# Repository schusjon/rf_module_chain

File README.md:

# Overview

The aim of the project is to develop a chain of RF-modules which can be connected in series. The most common connector for RF applications is the SMA connector. Because of the high purchase price, the idea to use another connector e.g. PCI Express has existed for quite some time. The main advantage over other connectors is the comparatively low price. Moreover, it can be used up to a frequency of about 500 MHz and the male connector can be easily included on the circuit board. 

[Bild 1]: images/chain.PNG
![Alt-Text][Bild 1]

A means of digital communication should be implemented throughout the chain, an expansion that distinguishes this project from previous, unfinished attempts. The high amount of contacts the PCI-E connector provides facilitates this endeavor.
The chain starts with a special start-module including pin headers for the power supply, as will be explained later.
We expect that the following voltages will cover most conceivable scenarios:

Voltage Rails

|  +5V | -5V  |  3.3V | +12V  | -12V  |
|---|---|---|---|---|

Again, the chosen PCI connector allows for all those different voltage rails and with a current handling of 1A per pin, distributing power to the chain can be done with the same connector.
To feed the chain with the RF-Signal, one SMA connector on the start-module is unavoidable. For further experiments it is useful to add two additional RF inputs. 
These can be used for a reference signal or any auxiliary signal. In this project we limit ourselves to designing only the traces and basic interfacing for these signals on the boards. 
To receive the signal from the chain, a further SMA connecter is used on the end module. 

## Signal Chain

The signal chain consists of different modules, all of which have a few components and properties in common:
All links within the chain are established with PCI-E 36 connectors, all modules bear either a straddle mount receptacle, card-edge fingers or both to interface with neighboring modules.
Each one is equipped with a STM32F0 microprocessor for data transmission and control purposes. 
They utilize their internal RC oscillator to help minimize cost and prevent clock spill into the RF signals.
A 4pin header is used to program these processors with a ST-Link USB adaptor. A fifth pin adjacent to the programming connector serves in conjunction with a jumper as a power switch for the processor on this module only. 
Connected during normal operation, the jumper can be removed to shut off the processor of a single module without cutting the power of the rest of the chain. (Due to the nature of the daisy chain, communication will be interrupted as well)
The modules incorporate separate ground planes for RF and data/power circuits. 
The RF ground is continuous on the back of the PCB to improve impedance control. Via stitching and a defined trace width and aura (1mm width, 0.15mm aura) of the RF signal traces on the 1.6mm FR4 PCBs yield an impedance close to 50 Ohms (with the properties of the laminate causing deviations). 
A series of solder pads on the modules allow linking those ground planes at virtually any point in the chain if the need arises.

[Bild 2]: images/bottom.PNG
![Alt-Text][Bild 2]

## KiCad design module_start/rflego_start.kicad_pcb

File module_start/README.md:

# Start Module

**The input/start module** additionally features input connectivity for power and signals:

Standard 2.54mm pin headers serve as power inputs, thus allowing for easy assembly of custom breakout cables. The same holds true for the RX and TX signals, enabling the user to use his favorite UART converter or control the chain with a single board computer. Additional ground pins might be added in following revisions to facilitate interfacing.

The RF signal has a female SMA receptacle, the two additional signals (REF and AUX) terminate to solder pads that allow connection of coax cables or pin headers.

The input module also hosts a 3.3V regulator that supplies the whole chain. Solder pads are prepared for different types of SOT 23-5 LDOs with their respective circuitry.

At the moment, the installed processor does not add any exclusive functionality and is simply another link in the daisy chain. A possible future implementation would be the detection of input signals or power supply voltages to help troubleshoot larger experimental setups. Conversely, this component could be cut entirely for cost optimization. Especially with suitable detectors like the AD 8307 being in the 10€ price range.

[Bild 1]: images/start_description.PNG

![Alt-Text][Bild 1]

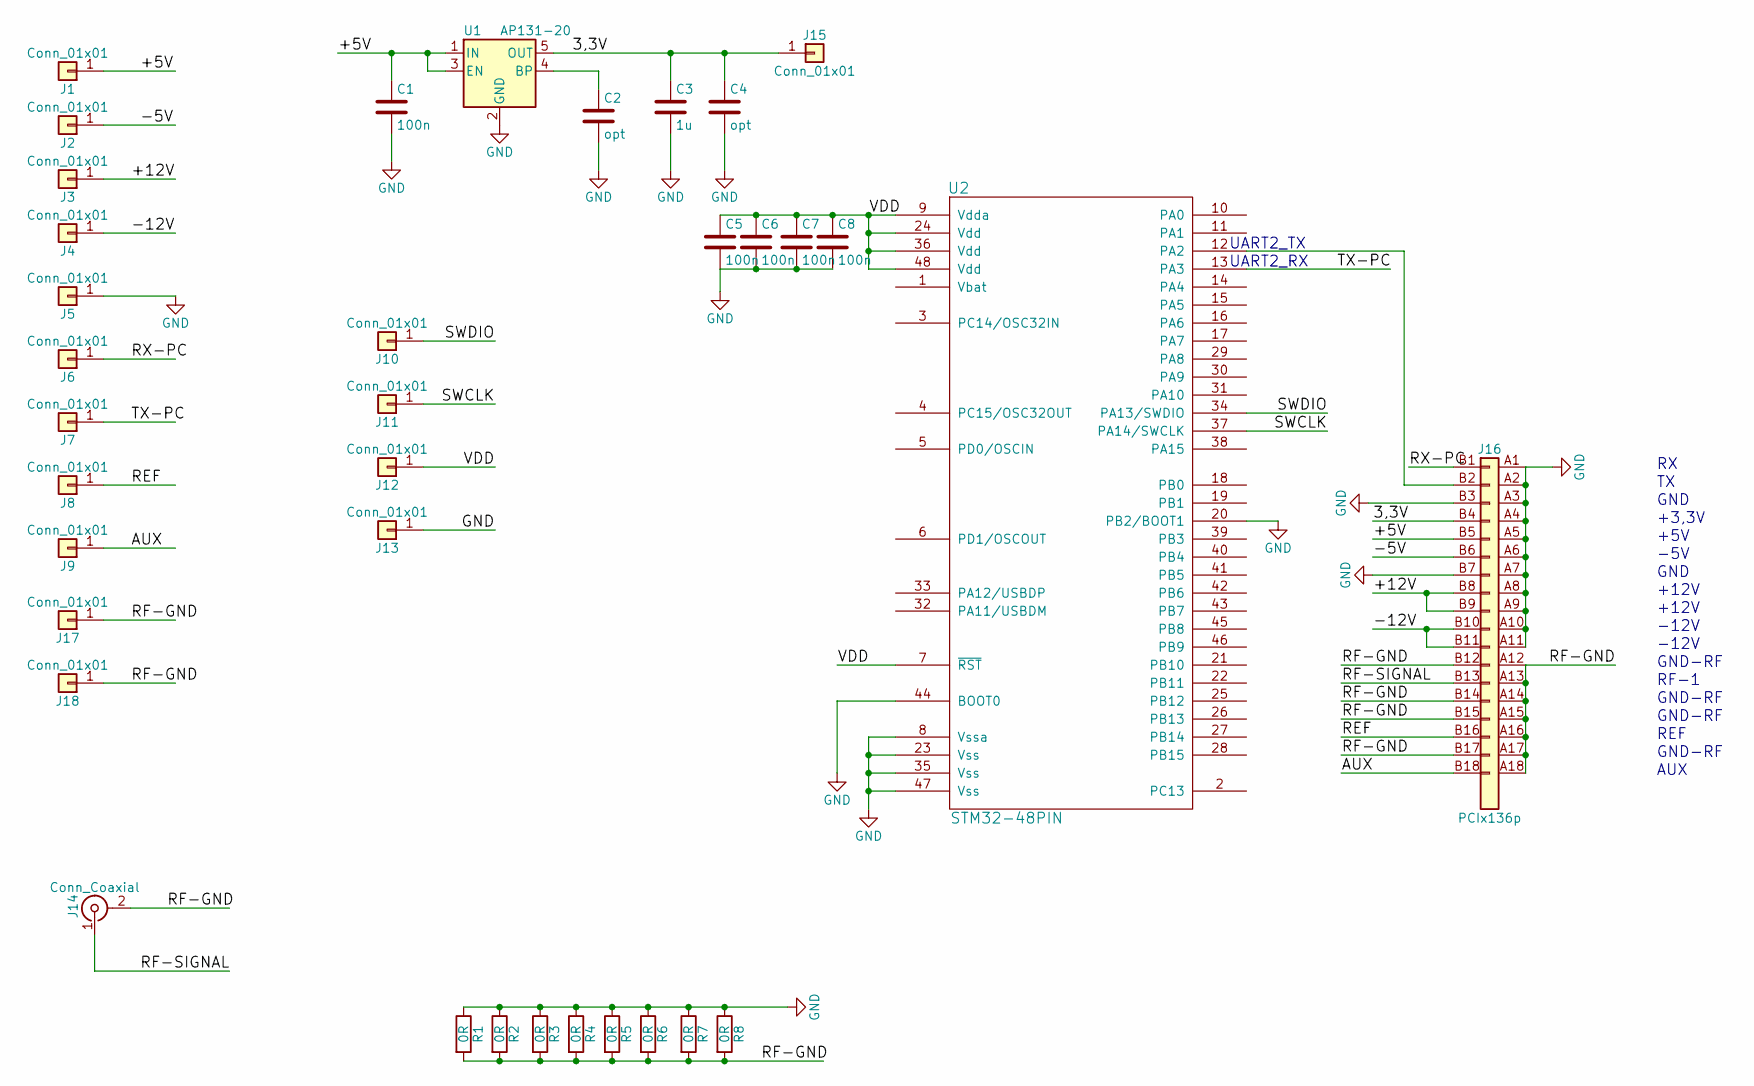
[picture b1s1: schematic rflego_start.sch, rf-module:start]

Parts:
C1, C5, C6, C7, C8: 100n; C_0603_HandSoldering
C2, C4: opt; C_0603_HandSoldering
C3: 1u; C_0603_HandSoldering
J1, J2, J3, J4, J5, J6, J7, J8, J9, J10, J11, J12, J13, J15, J17, J18: Conn_01x01; Pin_Header_Straight_1x01_Pitch2.54mm
J14: Conn_Coaxial; CONSMAEDGE
J16: PCIx136p; PCI-EXPRESS-SLOT
R1, R2, R3, R4, R5, R6, R7, R8: 0R; R_0603_HandSoldering
U1: AP131-20; SOT-23-5
U2: STM32-48PIN; LQFP-48_7x7mm_Pitch0.5mm

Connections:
/3,3V: C3.1, C4.1, J15.1, J16.B4 (Pin_4), U1.5 (OUT)
/+5V: C1.1, J1.1, J16.B5 (Pin_5), U1.1 (IN), U1.3 (EN)
/+12V: J3.1, J16.B8 (Pin_8), J16.B9 (Pin_9)
/-5V: J2.1, J16.B6 (Pin_6)
/-12V: J4.1, J16.B10 (Pin_10), J16.B11 (Pin_11)
/AUX: J9.1, J16.B18 (Pin_18)
/REF: J8.1, J16.B16 (Pin_16)
/RF-GND: J14.2 (Ext), J16.A12, J16.A13, J16.A14, J16.A15, J16.A16, J16.A17, J16.A18, J16.B12 (Pin_12), J16.B14 (Pin_14), J16.B15 (Pin_15), J16.B17 (Pin_17), J17.1, J18.1, R1.2, R2.2, R3.2, R4.2, R5.2, R6.2, R7.2, R8.2
/RF-SIGNAL: J14.1 (In), J16.B13 (Pin_13)
/RX-PC: J6.1, J16.B1 (Pin_1)
/SWCLK: J11.1, U2.37 (PA14/SWCLK)
/SWDIO: J10.1, U2.34 (PA13/SWDIO)
/TX-PC: J7.1, U2.13 (PA3)
/VDD: C5.1, C6.1, C7.1, C8.1, J12.1, U2.7 (~RST), U2.9 (Vdda), U2.24 (Vdd), U2.36 (Vdd), U2.48 (Vdd)
GND: C1.2, C2.2, C3.2, C4.2, C5.2, C6.2, C7.2, C8.2, J5.1, J13.1, J16.A1 (Pin_19), J16.A2 (Pin_20), J16.A3, J16.A4, J16.A5, J16.A6, J16.A7, J16.A8, J16.A9, J16.A10, J16.A11, J16.B3 (Pin_3), J16.B7 (Pin_7), R1.1, R2.1, R3.1, R4.1, R5.1, R6.1, R7.1, R8.1, U1.2 (GND), U2.8 (Vssa), U2.20 (PB2/BOOT1), U2.23 (Vss), U2.35 (Vss), U2.44 (BOOT0), U2.47 (Vss)
unnamed: C2.1, U1.4 (BP)
unnamed: J16.B2 (Pin_2), U2.12 (PA2)

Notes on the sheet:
GND
+3,3V
+5V
-5V
+12V
-12V
GND-RF
RF-1
REF
AUX
UART2_TX
UART2_RX

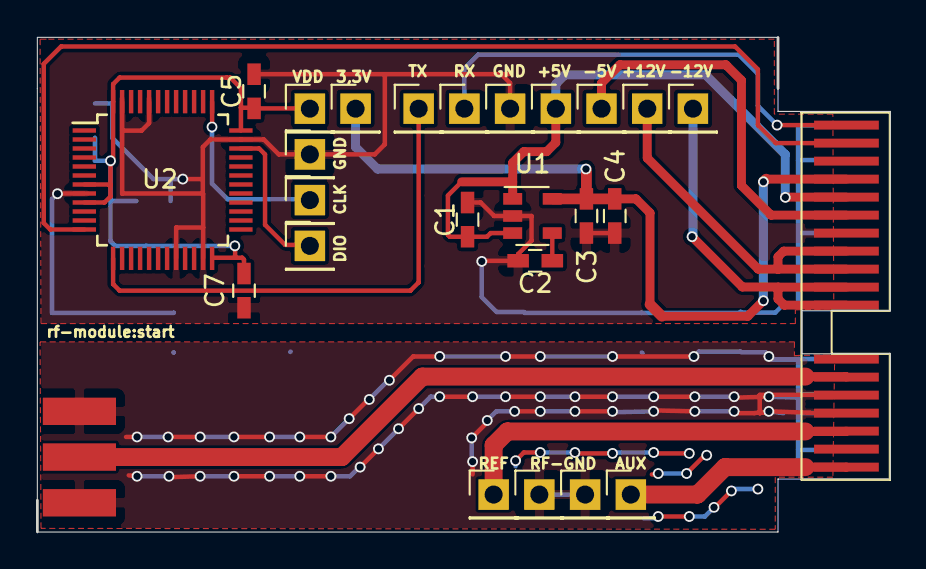
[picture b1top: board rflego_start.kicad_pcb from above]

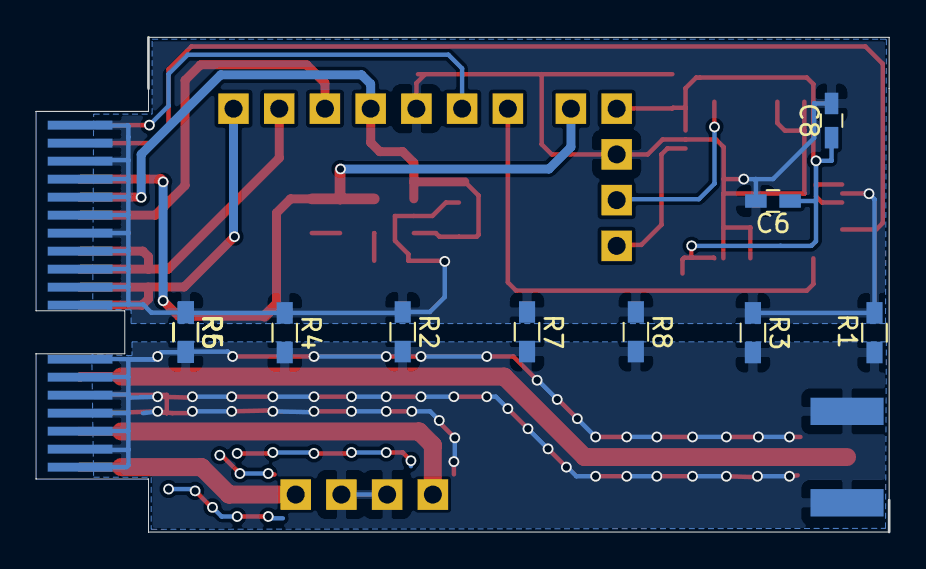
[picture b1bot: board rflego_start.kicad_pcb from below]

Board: 2 copper layers, 47.3 x 27.5 mm, 36 parts (10 on the bottom side), 17 nets.

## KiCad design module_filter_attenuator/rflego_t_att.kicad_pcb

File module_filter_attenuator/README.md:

# Filter Attenuator Modules

**The filter/attenuator modules** come in two topologies, PI and T. Solder pads (0603 in metric system) allow for custom filters and attenuators. Identical except for the filter configuration, both modules pass REF and AUX unaltered. The processor can be programmed with information about the implemented filter, making its properties computer-readable. While it does not provide any control functionality at this moment, it is conceivable to utilize RF switches to select different attenuations or frequencies. (the SKY 13XXX range from Skyworks Solutions appears to be promising and cost effective)

The prototype PI-attenuator was equipped with 18 Ohms for R7 and R9 and 300 ohms for R8, selected from the E24 series.

The calculated values for 3dB attenuation would have been 17.6 ohms and 292 ohms respectively.

The T attenuator was implemented with 10dB of attenuation, with  the resistor values 27 and 36 ohms ( instead of the theoretical 26.0 and 35.1 ohms)

[Bild 1]: images/bottom-pi-att.PNG

![Alt-Text][Bild 1]

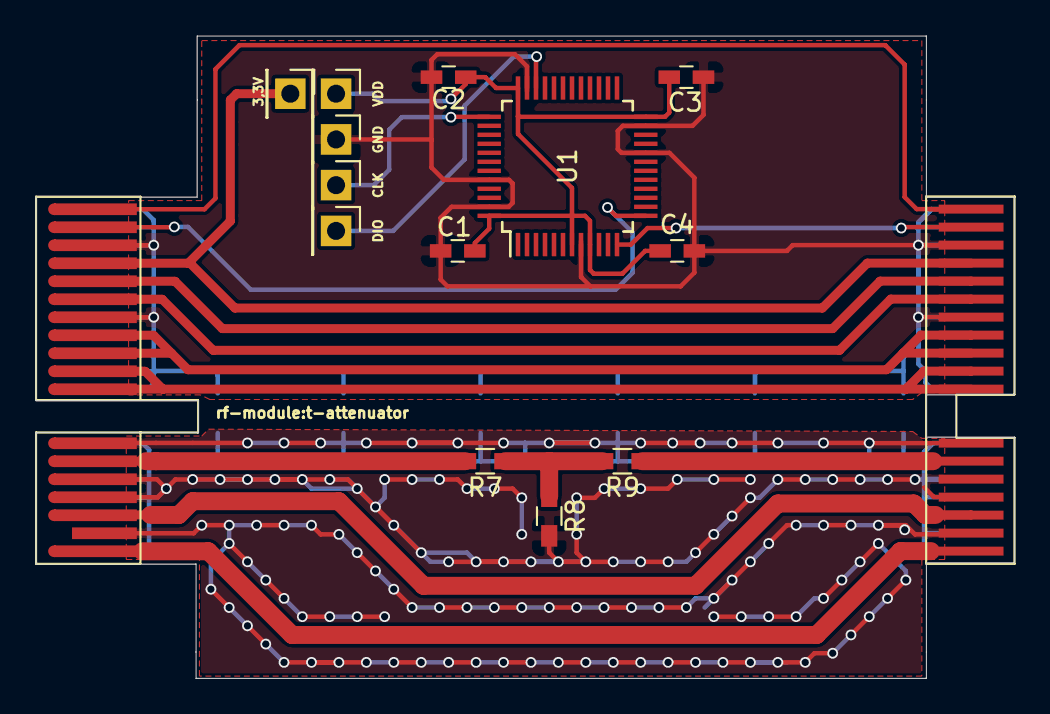
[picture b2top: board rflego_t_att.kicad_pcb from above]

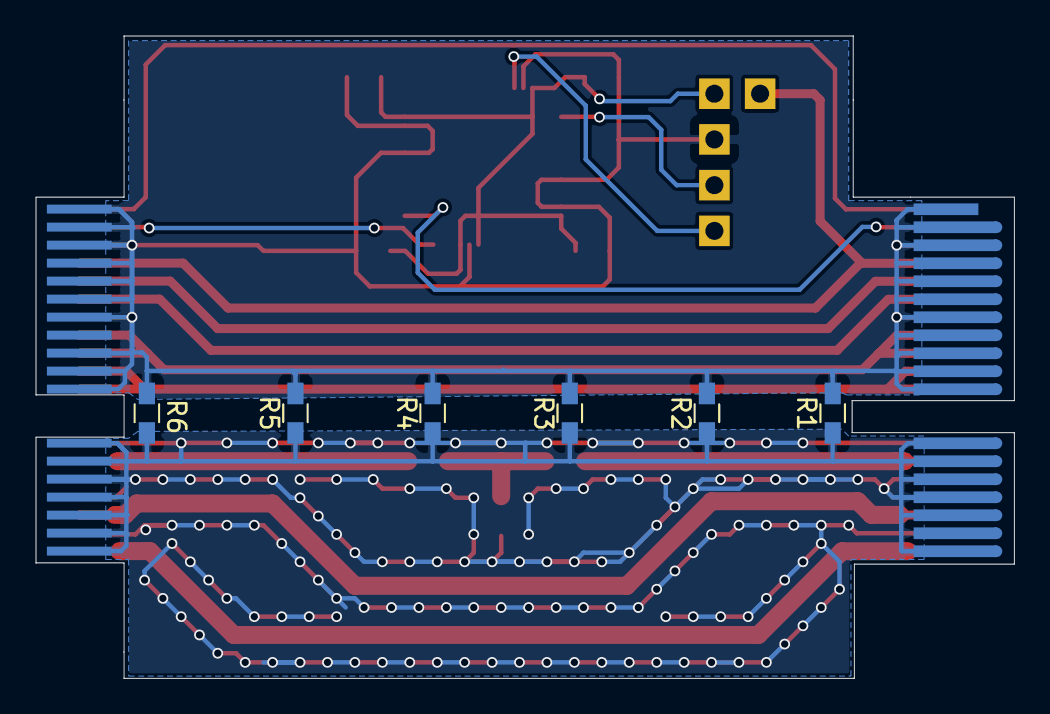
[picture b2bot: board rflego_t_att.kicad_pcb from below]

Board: 2 copper layers, 54.4 x 35.7 mm, 21 parts (6 on the bottom side), 18 nets.

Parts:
3,3V: Conn_01x01; Pin_Header_Straight_1x01_Pitch2.54mm
C1, C2, C3, C4: 100nF; C_0603_HandSoldering
CLK: Conn_01x01; Pin_Header_Straight_1x01_Pitch2.54mm
DIO: Conn_01x01; Pin_Header_Straight_1x01_Pitch2.54mm
GND: Conn_01x01; Pin_Header_Straight_1x01_Pitch2.54mm
J1: PCIx136p; PCI-EXPRESS
J12: PCIx136p Slot; PCI-EXPRESS-SLOT
R1, R2, R3, R4, R5, R6: 0; R_0603_HandSoldering
R7, R8, R9: ?; R_0603_HandSoldering
U1: STM32-48PIN; LQFP-48_7x7mm_Pitch0.5mm
VDD: Conn_01x01; Pin_Header_Straight_1x01_Pitch2.54mm

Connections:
/3,3V: 3,3V.1, J1.B4, J12.B4
/+5V: J1.B5, J12.B5
/+12V: J1.B8, J1.B9, J12.B8, J12.B9
/-5V: J1.B6, J12.B6
/-12V: J1.B10, J1.B11, J12.B10, J12.B11
/AUX: J1.B18, J12.B18
/REF: J1.B16, J12.B16
/RF-GND: J1.A12, J1.A13, J1.A14, J1.A15, J1.A16, J1.A17, J1.A18, J1.B12, J1.B14, J1.B15, J1.B17, J12.A12, J12.A13, J12.A14, J12.A15, J12.A16, J12.A17, J12.A18, J12.B12, J12.B14, J12.B15, J12.B17, R1.1, R2.1, R3.1, R4.1, R5.1, R6.1, R8.2
/RF-IN: J1.B13, R7.2
/RF-OUT: J12.B13, R9.1
/RX: J1.B2, U1.13
/RX-PC: J1.B1, J12.B1
/SWCLK: CLK.1, U1.37
/SWDIO: DIO.1, U1.34
/TX: J12.B2, U1.12
/VDD: C1.1, C2.1, C3.1, C4.1, U1.7, U1.9, U1.24, U1.36, U1.48, VDD.1
GND: C1.2, C2.2, C3.2, C4.2, GND.1, J1.A1, J1.A2, J1.A3, J1.A4, J1.A5, J1.A6, J1.A7, J1.A8, J1.A9, J1.A10, J1.A11, J1.B3, J1.B7, J12.A1, J12.A2, J12.A3, J12.A4, J12.A5, J12.A6, J12.A7, J12.A8, J12.A9, J12.A10, J12.A11, J12.B3, J12.B7, R1.2, R2.2, R3.2, R4.2, R5.2, R6.2, U1.8, U1.20, U1.23, U1.35, U1.44, U1.47
unnamed: R7.1, R8.1, R9.2

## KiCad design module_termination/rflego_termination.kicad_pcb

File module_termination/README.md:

# Termination Module

**The termination/end module** includes status LEDs to check the power busses and the link status of the chain. Two of them are controlled by the uC and are user programmable. The two additional RF signals, REF and AUX are terminated on the module with 50 ohms.

The output is implemented as a female SMA receptacle.

The prototype carries its own 3.3V LDO due to the critical role of the embedded processor. This last link in the chain reorganizes all data received from preceding modules and transmits them to the control computer. This individual power supply could have offered additional debugging and troubleshooting information but was deemed unnecessary in early test and was therefore omitted from later designs.

Further development could include an automated power supply check: A passive resistor network of voltage dividers and pullups should be enough to generate an unambiguous digital pattern that would enable the uC to read the status of the connected supplies.

[Bild 1]: images/bottom_termination.PNG

![Alt-Text][Bild 1]

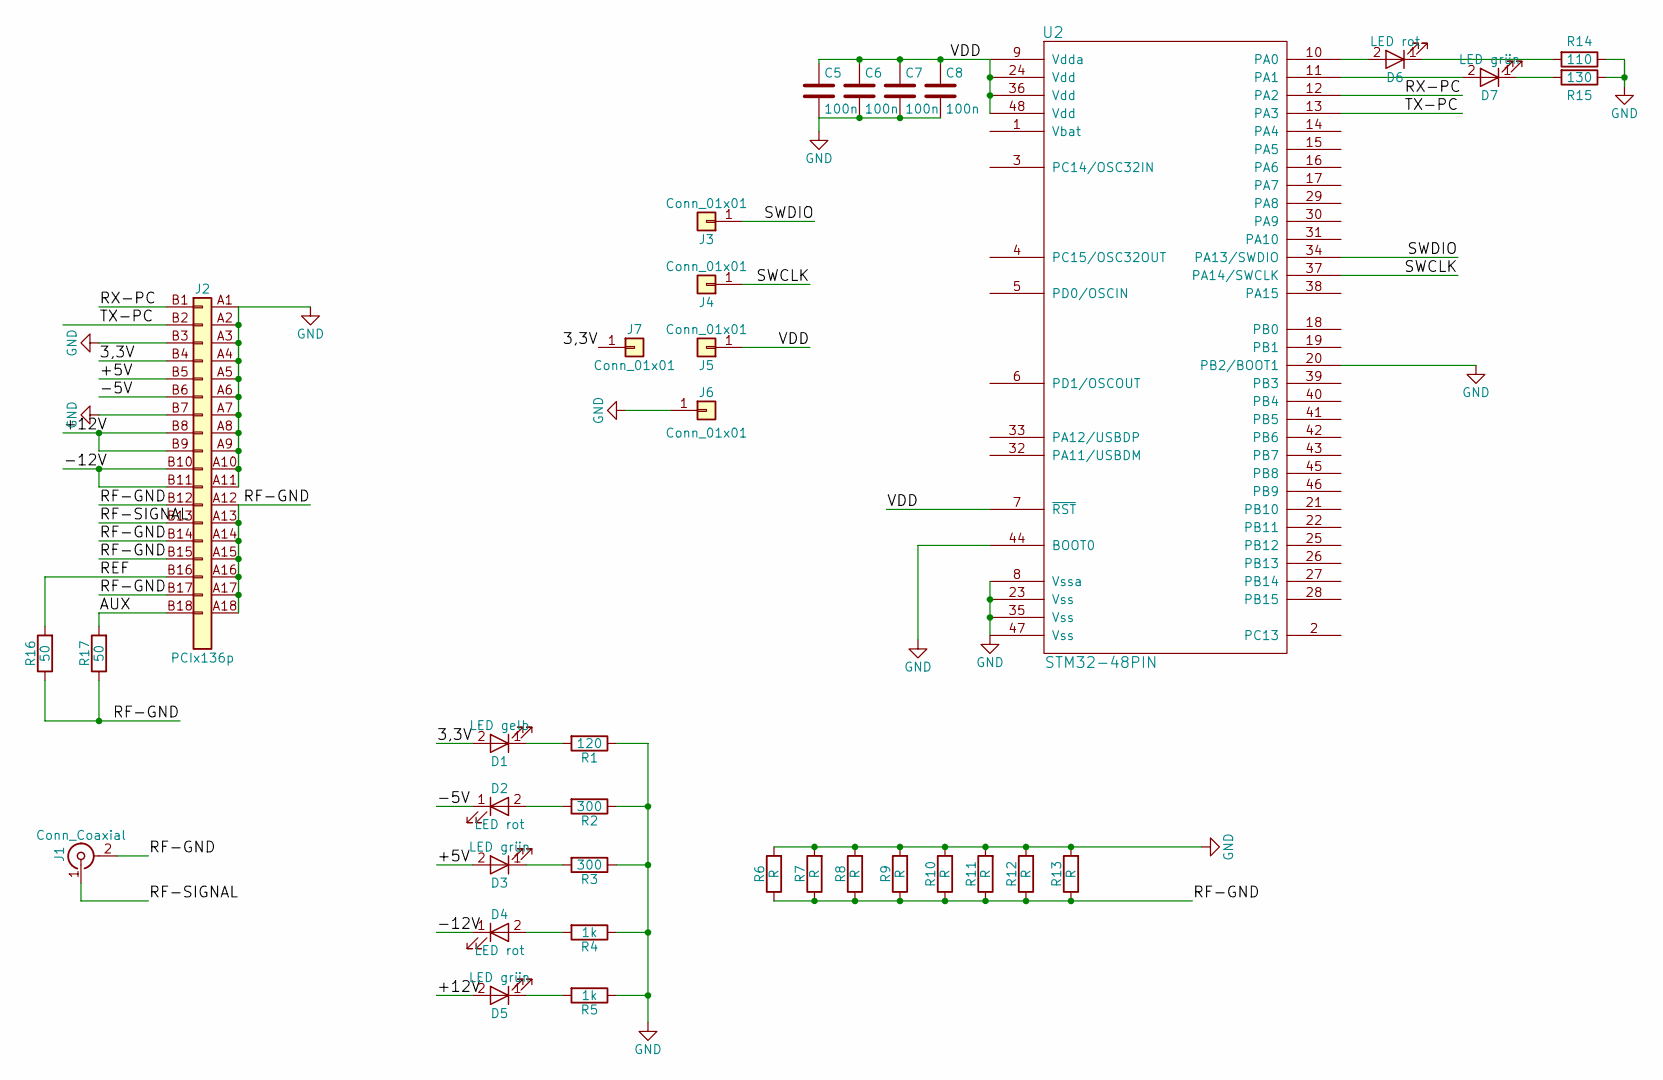
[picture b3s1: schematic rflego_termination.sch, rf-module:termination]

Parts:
C5, C6, C7, C8: 100n; C_0603_HandSoldering
D1: LED gelb; LED_0603_HandSoldering
D2, D4, D6: LED rot; LED_0603_HandSoldering
D3, D5, D7: LED grün; LED_0603_HandSoldering
J1: Conn_Coaxial; CON-SMA-EDGE
J2: PCIx136p; PCI-EXPRESS
J3, J4, J5, J6, J7: Conn_01x01; Pin_Header_Straight_1x01_Pitch2.54mm
R1: 120; R_0603_HandSoldering
R2, R3: 300; R_0603_HandSoldering
R4, R5: 1k; R_0603_HandSoldering
R6, R7, R8, R9, R10, R11, R12, R13: R; R_0603_HandSoldering
R14: 110; R_0603_HandSoldering
R15: 130; R_0603_HandSoldering
R16, R17: 50; R_0603_HandSoldering
U2: STM32-48PIN; LQFP-48_7x7mm_Pitch0.5mm

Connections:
/3,3V: D1.2 (A), J2.B4 (Pin_4), J7.1
/+5V: D3.2 (A), J2.B5 (Pin_5)
/+12V: D5.2 (A), J2.B8 (Pin_8), J2.B9 (Pin_9)
/-5V: D2.1 (K), J2.B6 (Pin_6)
/-12V: D4.1 (K), J2.B10 (Pin_10), J2.B11 (Pin_11)
/AUX: J2.B18 (Pin_18), R17.2
/REF: J2.B16 (Pin_16), R16.2
/RF-GND: J1.2 (Ext), J2.A12, J2.A13, J2.A14, J2.A15, J2.A16, J2.A17, J2.A18, J2.B12 (Pin_12), J2.B14 (Pin_14), J2.B15 (Pin_15), J2.B17 (Pin_17), R6.1, R7.1, R8.1, R9.1, R10.1, R11.1, R12.1, R13.1, R16.1, R17.1
/RF-SIGNAL: J1.1 (In), J2.B13 (Pin_13)
/RX-PC: J2.B1 (Pin_1), U2.12 (PA2)
/SWCLK: J4.1, U2.37 (PA14/SWCLK)
/SWDIO: J3.1, U2.34 (PA13/SWDIO)
/TX-PC: J2.B2 (Pin_2), U2.13 (PA3)
/VDD: C5.1, C6.1, C7.1, C8.1, J5.1, U2.7 (~RST), U2.9 (Vdda), U2.24 (Vdd), U2.36 (Vdd), U2.48 (Vdd)
GND: C5.2, C6.2, C7.2, C8.2, J2.A1 (Pin_19), J2.A2 (Pin_20), J2.A3, J2.A4, J2.A5, J2.A6, J2.A7, J2.A8, J2.A9, J2.A10, J2.A11, J2.B3 (Pin_3), J2.B7 (Pin_7), J6.1, R1.1, R2.1, R3.1, R4.1, R5.1, R6.2, R7.2, R8.2, R9.2, R10.2, R11.2, R12.2, R13.2, R14.1, R15.1, U2.8 (Vssa), U2.20 (PB2/BOOT1), U2.23 (Vss), U2.35 (Vss), U2.44 (BOOT0), U2.47 (Vss)
unnamed: D1.1 (K), R1.2
unnamed: D2.2 (A), R2.2
unnamed: D3.1 (K), R3.2
unnamed: D4.2 (A), R4.2
unnamed: D5.1 (K), R5.2
unnamed: D6.1 (K), R14.2
unnamed: D6.2 (A), U2.10 (PA0)
unnamed: D7.1 (K), R15.2
unnamed: D7.2 (A), U2.11 (PA1)

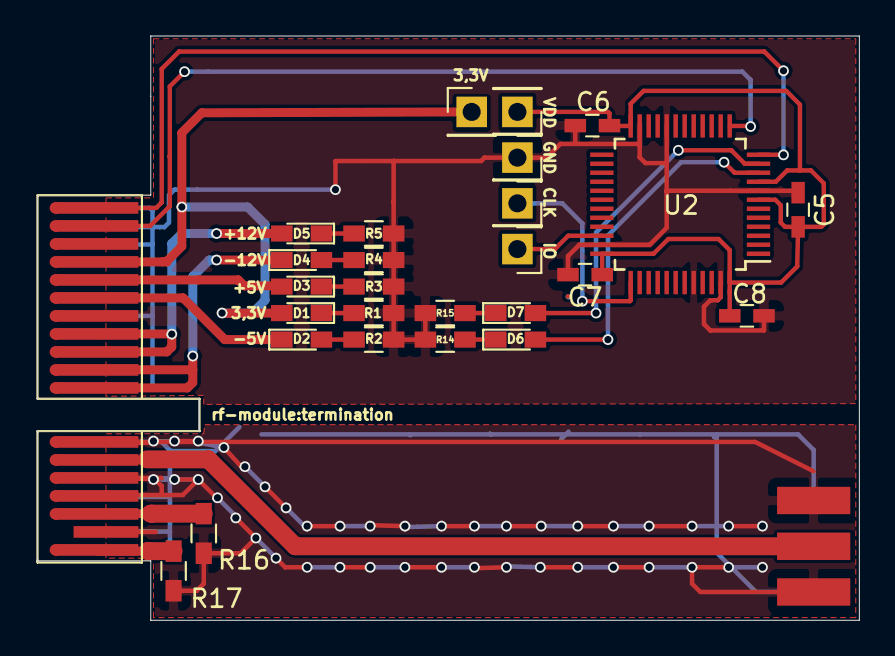
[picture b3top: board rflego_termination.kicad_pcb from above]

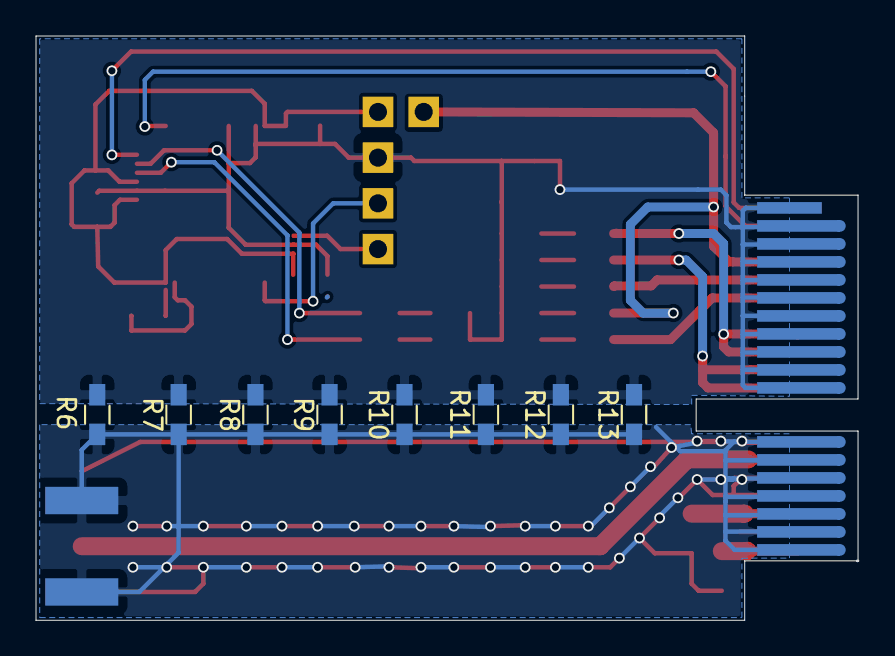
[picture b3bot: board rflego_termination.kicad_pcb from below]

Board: 2 copper layers, 45.6 x 32.3 mm, 36 parts (8 on the bottom side), 24 nets.

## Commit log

2018-07-12 init repository
2019-01-12 add sketch_termination
2019-01-12 add sketch_module_without_ValueInEEPROM
2019-01-12 add sketch_start
2019-01-12 add serial communication
